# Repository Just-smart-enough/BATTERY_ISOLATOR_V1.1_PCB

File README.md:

# BATTERY_ISOLATOR_V1.1_PCB
A prototype 12V RV battery isolator using a STM32F042F6P6 processor, an ACS724 current sensor and a MCP2551 CAN Transceiver.  
Intention is to PWM current flow based on max current parameters and voltage differences between the two batteries. 
It will also broadcast both battery's voltage and the charging current over CANbus

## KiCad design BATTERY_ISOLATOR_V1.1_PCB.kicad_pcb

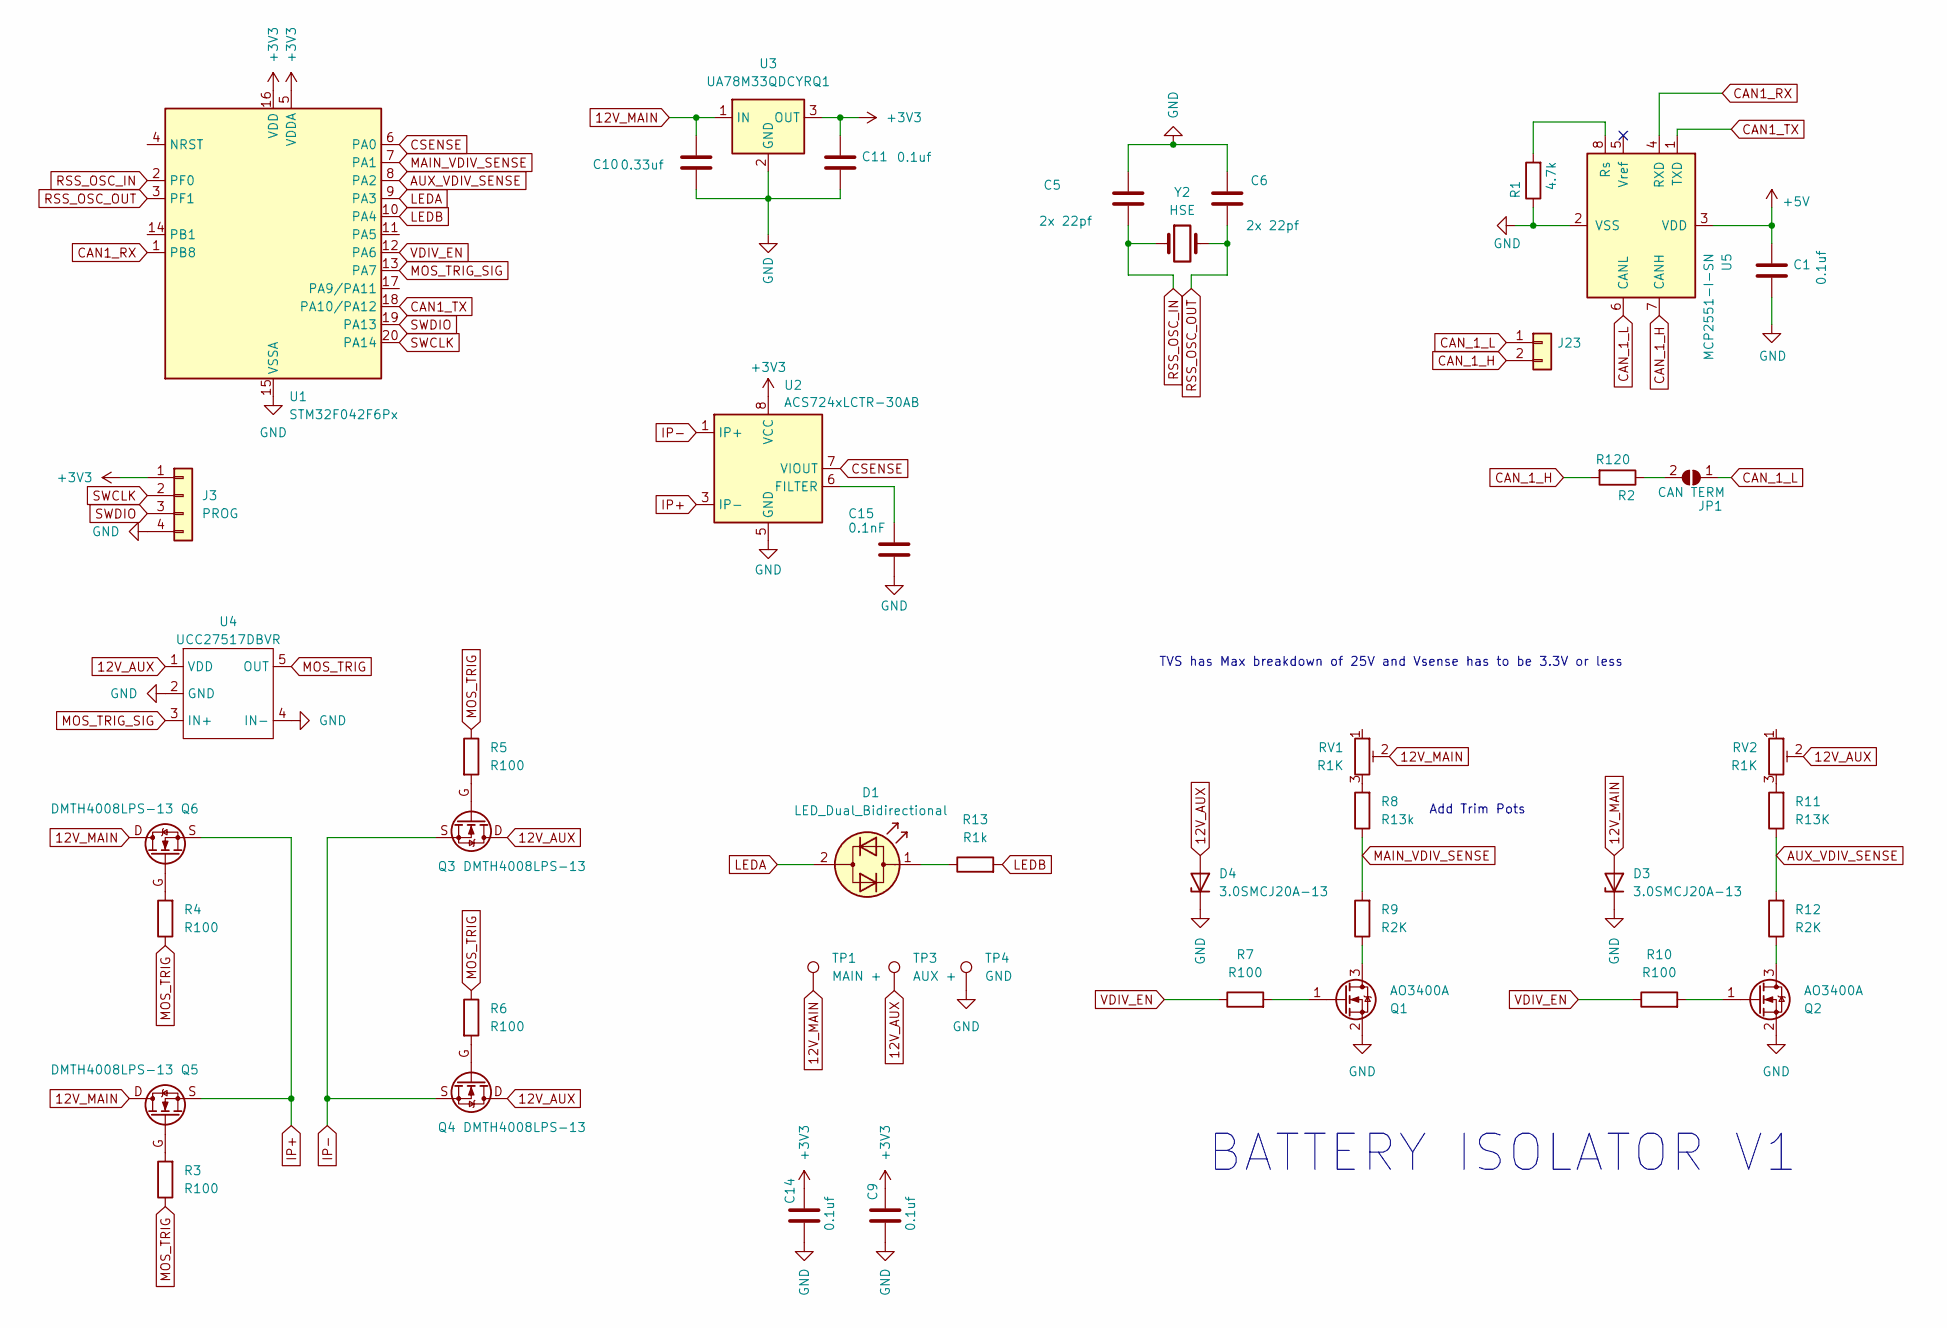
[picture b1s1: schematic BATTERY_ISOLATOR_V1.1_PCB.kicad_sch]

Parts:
C1: 0.1uf; C_0805_2012Metric
C5, C6: 2x 22pf; C_0805_2012Metric
C9, C11, C14: 0.1uf; C_0603_1608Metric
C10: 0.33uf; C_0603_1608Metric
C15: 0.1nF; C_0402_1005Metric
D1: LED_Dual_Bidirectional; LED_D5.0mm
D3, D4: 3.0SMCJ20A-13; D_SMC
J3: PROG; PinHeader_1x04_P1.27mm_Vertical
J23: CAN 1; JST_XH_B2B-XH-A_1x02_P2.50mm_Vertical
JP1: CAN TERM; PinHeader_1x02_P2.54mm_Vertical
Q1, Q2: AO3400A; SOT-23
Q3, Q4, Q5, Q6: DMTH4008LPS-13; DMTH4008LPS-13(DI5060-8)
R1: 4.7k; R_0603_1608Metric
R2: R120; R_0603_1608Metric
R3, R4, R5, R6, R7, R10: R100; R_0603_1608Metric
R8: R13k; R_0603_1608Metric
R9, R12: R2K; R_0603_1608Metric
R11: R13K; R_0603_1608Metric
R13: R1k; R_0603_1608Metric
RV1, RV2: R1K; Potentiometer_Bourns_TC33X_Vertical
TP1: MAIN +; SAMZO 8060500M4
TP3: AUX +; SAMZO 8060500M4
TP4: GND; SAMZO 8060500M4
U1: STM32F042F6Px; TSSOP-20_4.4x6.5mm_P0.65mm
U2: ACS724xLCTR-30AB; SOIC-8_3.9x4.9mm_P1.27mm
U3: UA78M33QDCYRQ1; SOT-223-3_TabPin2
U4: UCC27517DBVR; SOT-23-5
U5: MCP2551-I-SN; SOIC-8_3.9x4.9mm_P1.27mm
Y2: HSE; Crystal_SMD_5032-2Pin_5.0x3.2mm

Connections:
12V_AUX: D4.2 (A), Q3.D, Q4.D, RV2.2, TP3.1, U4.1 (VDD)
12V_MAIN: C10.1, D3.2 (A), Q5.D, Q6.D, RV1.2, TP1.1, U3.1 (IN)
+3V3: C9.1, C11.1, C14.1, J3.1, U1.5 (VDDA), U1.16 (VDD), U2.8 (VCC), U3.3 (OUT)
+5V: C1.1, U5.3 (VDD)
AUX_VDIV_SENSE: R11.1, R12.2, U1.8 (PA2)
CAN1_RX: U1.1 (PB8), U5.4 (RXD)
CAN1_TX: U1.18 (PA10/PA12), U5.1 (TXD)
CAN_1_H: J23.2, R2.2, U5.7 (CANH)
CAN_1_L: J23.1, JP1.1 (A), U5.6 (CANL)
CSENSE: U1.6 (PA0), U2.7 (VIOUT)
GND: C1.2, C5.1, C6.1, C9.2, C10.2, C11.2, C14.2, C15.2, D3.1 (K), D4.1 (K), J3.4, Q1.2 (S), Q2.2 (S), R1.1, TP4.1, U1.15 (VSSA), U2.5 (GND), U3.2 (GND), U4.2 (GND), U4.4 (IN-), U5.2 (VSS)
IP+: Q5.S, Q6.S, U2.3 (IP-), U2.4 (IP-)
IP-: Q3.S, Q4.S, U2.1 (IP+), U2.2 (IP+)
LEDA: D1.2 (AK), U1.9 (PA3)
LEDB: R13.2, U1.10 (PA4)
MAIN_VDIV_SENSE: R8.1, R9.2, U1.7 (PA1)
MOS_TRIG: R3.1, R4.1, R5.1, R6.1, U4.5 (OUT)
MOS_TRIG_SIG: U1.13 (PA7), U4.3 (IN+)
unnamed: D1.1 (KA), R13.1
unnamed: JP1.2 (B), R2.1
unnamed: Q1.3 (D), R9.1
unnamed: Q1.1 (G), R7.2
unnamed: Q2.3 (D), R12.1
unnamed: Q2.1 (G), R10.2
unnamed: Q3.G, R5.2
unnamed: Q4.G, R6.2
unnamed: Q5.G, R3.2
unnamed: Q6.G, R4.2
unnamed: R8.2, RV1.3
unnamed: R11.2, RV2.3
unnamed: C15.1, U2.6 (FILTER)
unnamed: R1.2, U5.8 (Rs)
RSS_OSC_IN: C5.2, U1.2 (PF0), Y2.1
RSS_OSC_OUT: C6.2, U1.3 (PF1), Y2.2
SWCLK: J3.2, U1.20 (PA14)
SWDIO: J3.3, U1.19 (PA13)
VDIV_EN: R7.1, R10.1, U1.12 (PA6)

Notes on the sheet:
BATTERY ISOLATOR V1
TVS has Max breakdown of 25V and Vsense has to be 3.3V or less
Add Trim Pots

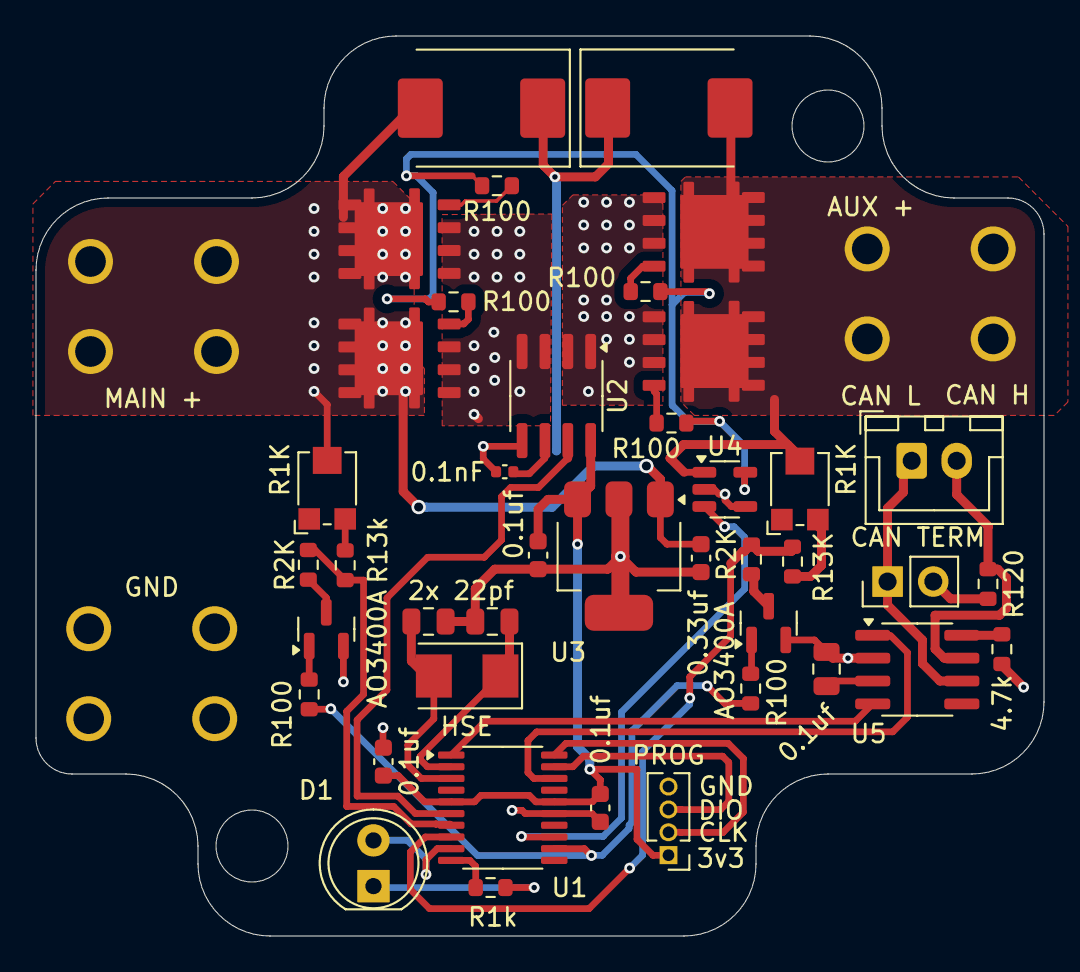
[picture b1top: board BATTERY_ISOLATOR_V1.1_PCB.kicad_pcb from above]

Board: 2 copper layers, 56.0 x 50.0 mm, 44 parts (0 on the bottom side), 37 nets.

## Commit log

2025-06-17 Updated files
    Added initial schematic and layout
2025-06-19 Added bicolor LED and Switch 3V3 source to 12V Main
